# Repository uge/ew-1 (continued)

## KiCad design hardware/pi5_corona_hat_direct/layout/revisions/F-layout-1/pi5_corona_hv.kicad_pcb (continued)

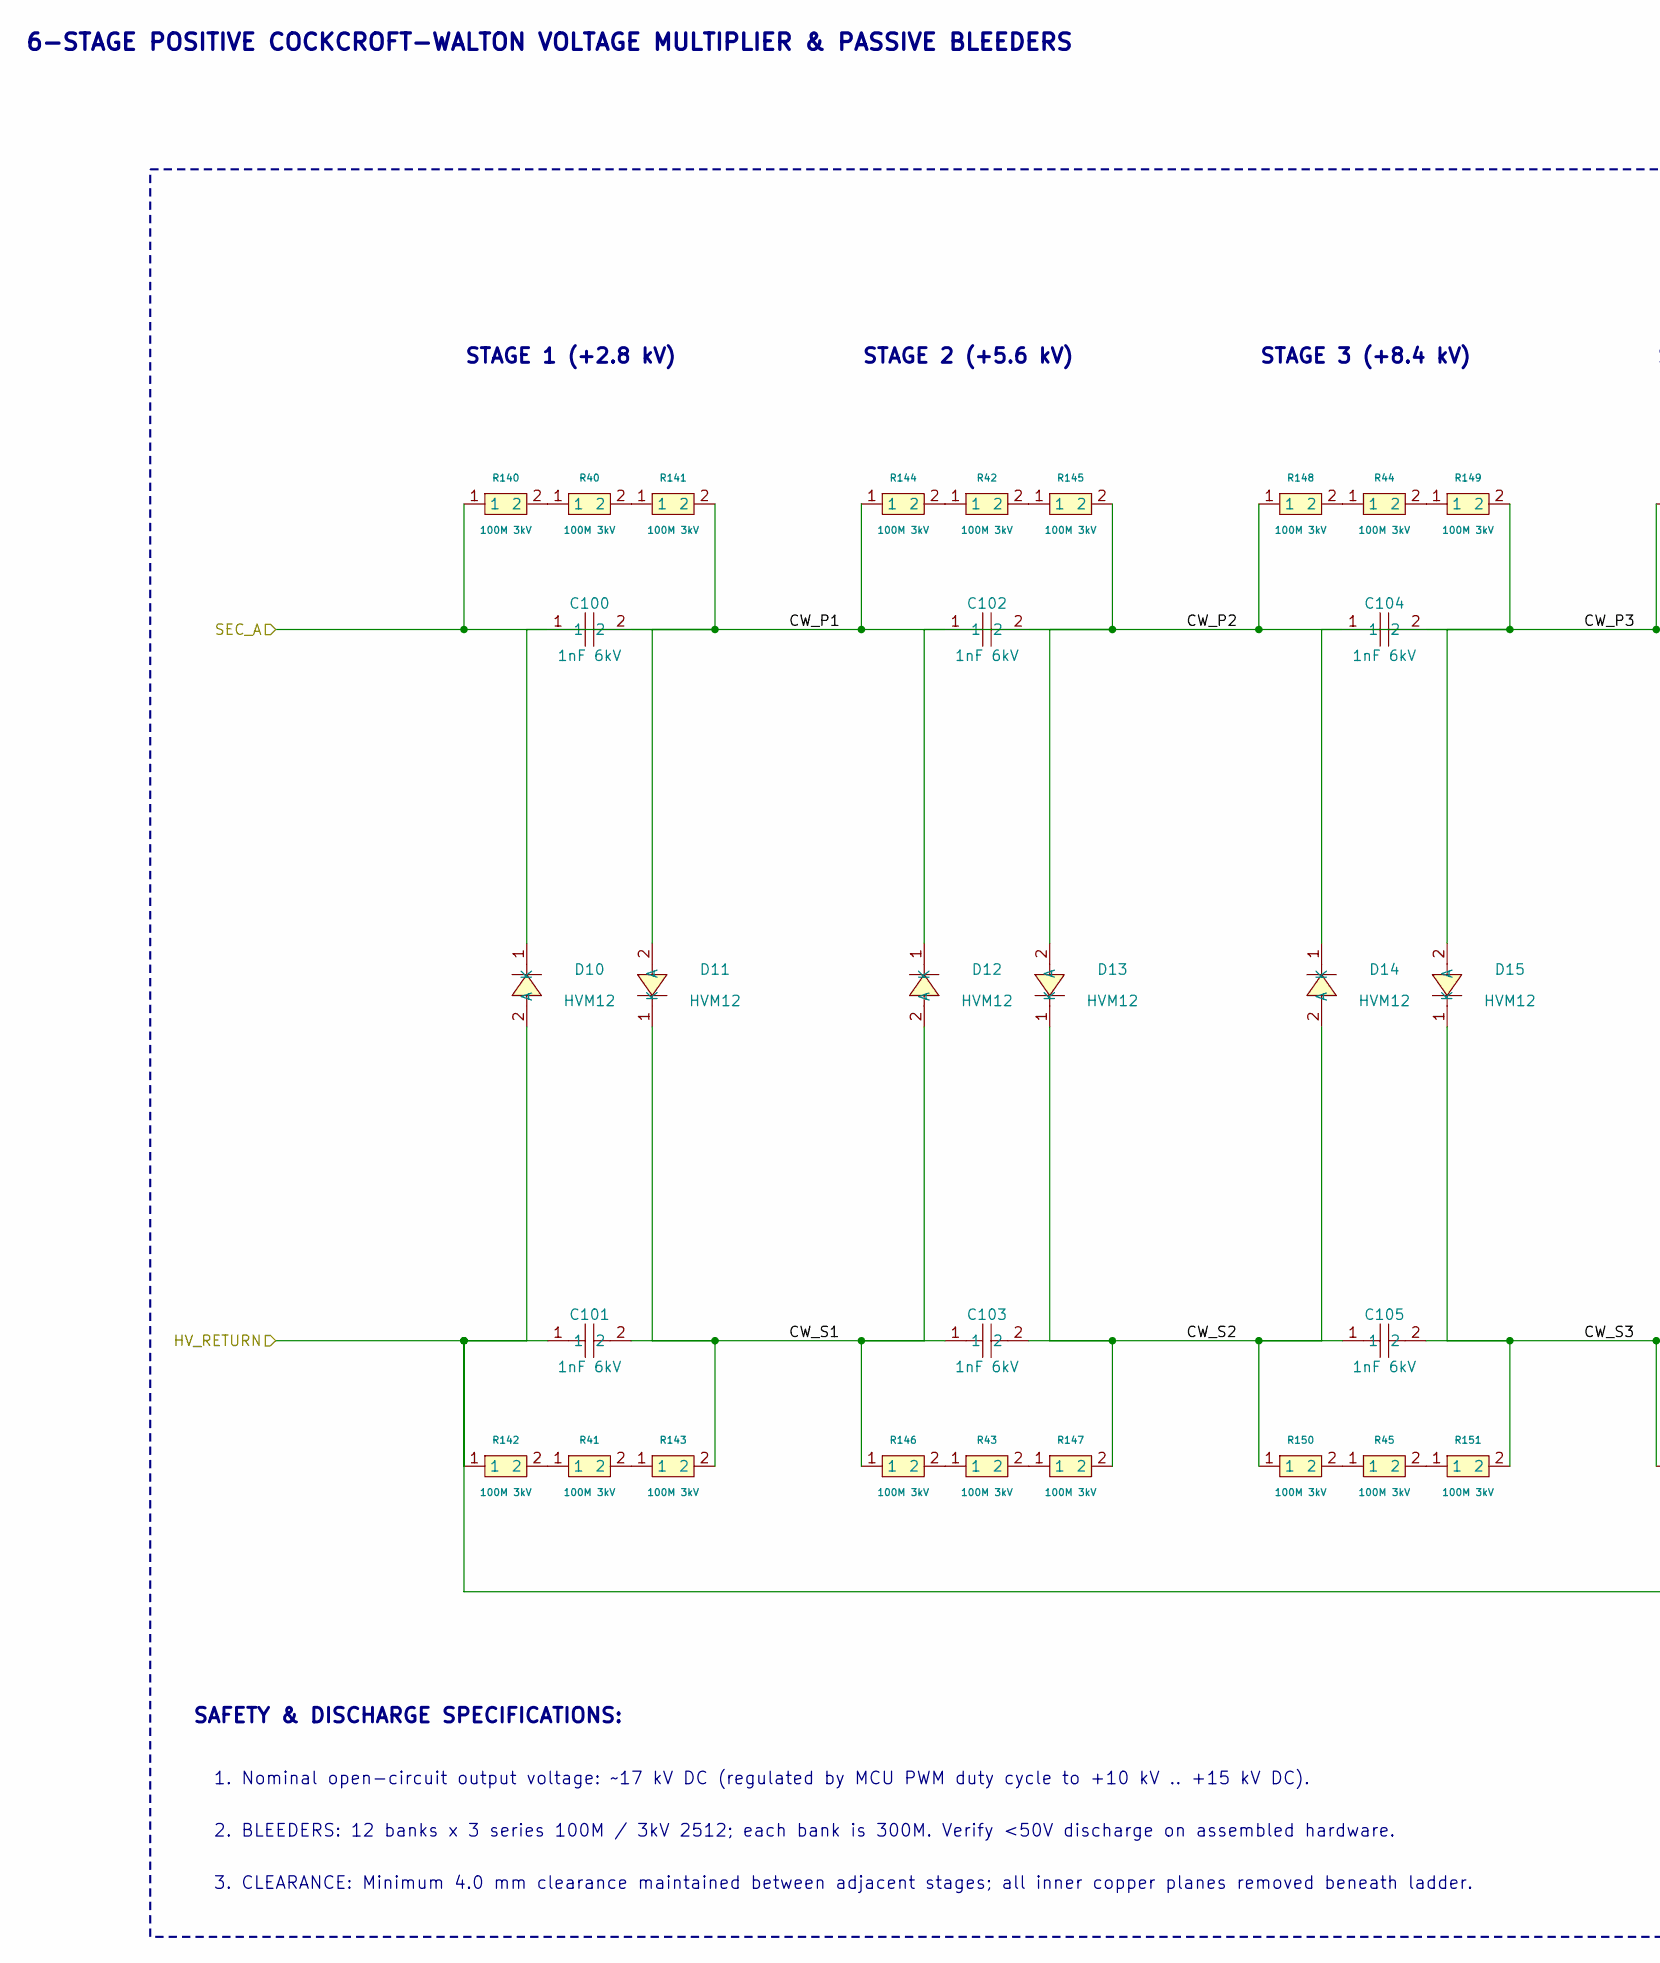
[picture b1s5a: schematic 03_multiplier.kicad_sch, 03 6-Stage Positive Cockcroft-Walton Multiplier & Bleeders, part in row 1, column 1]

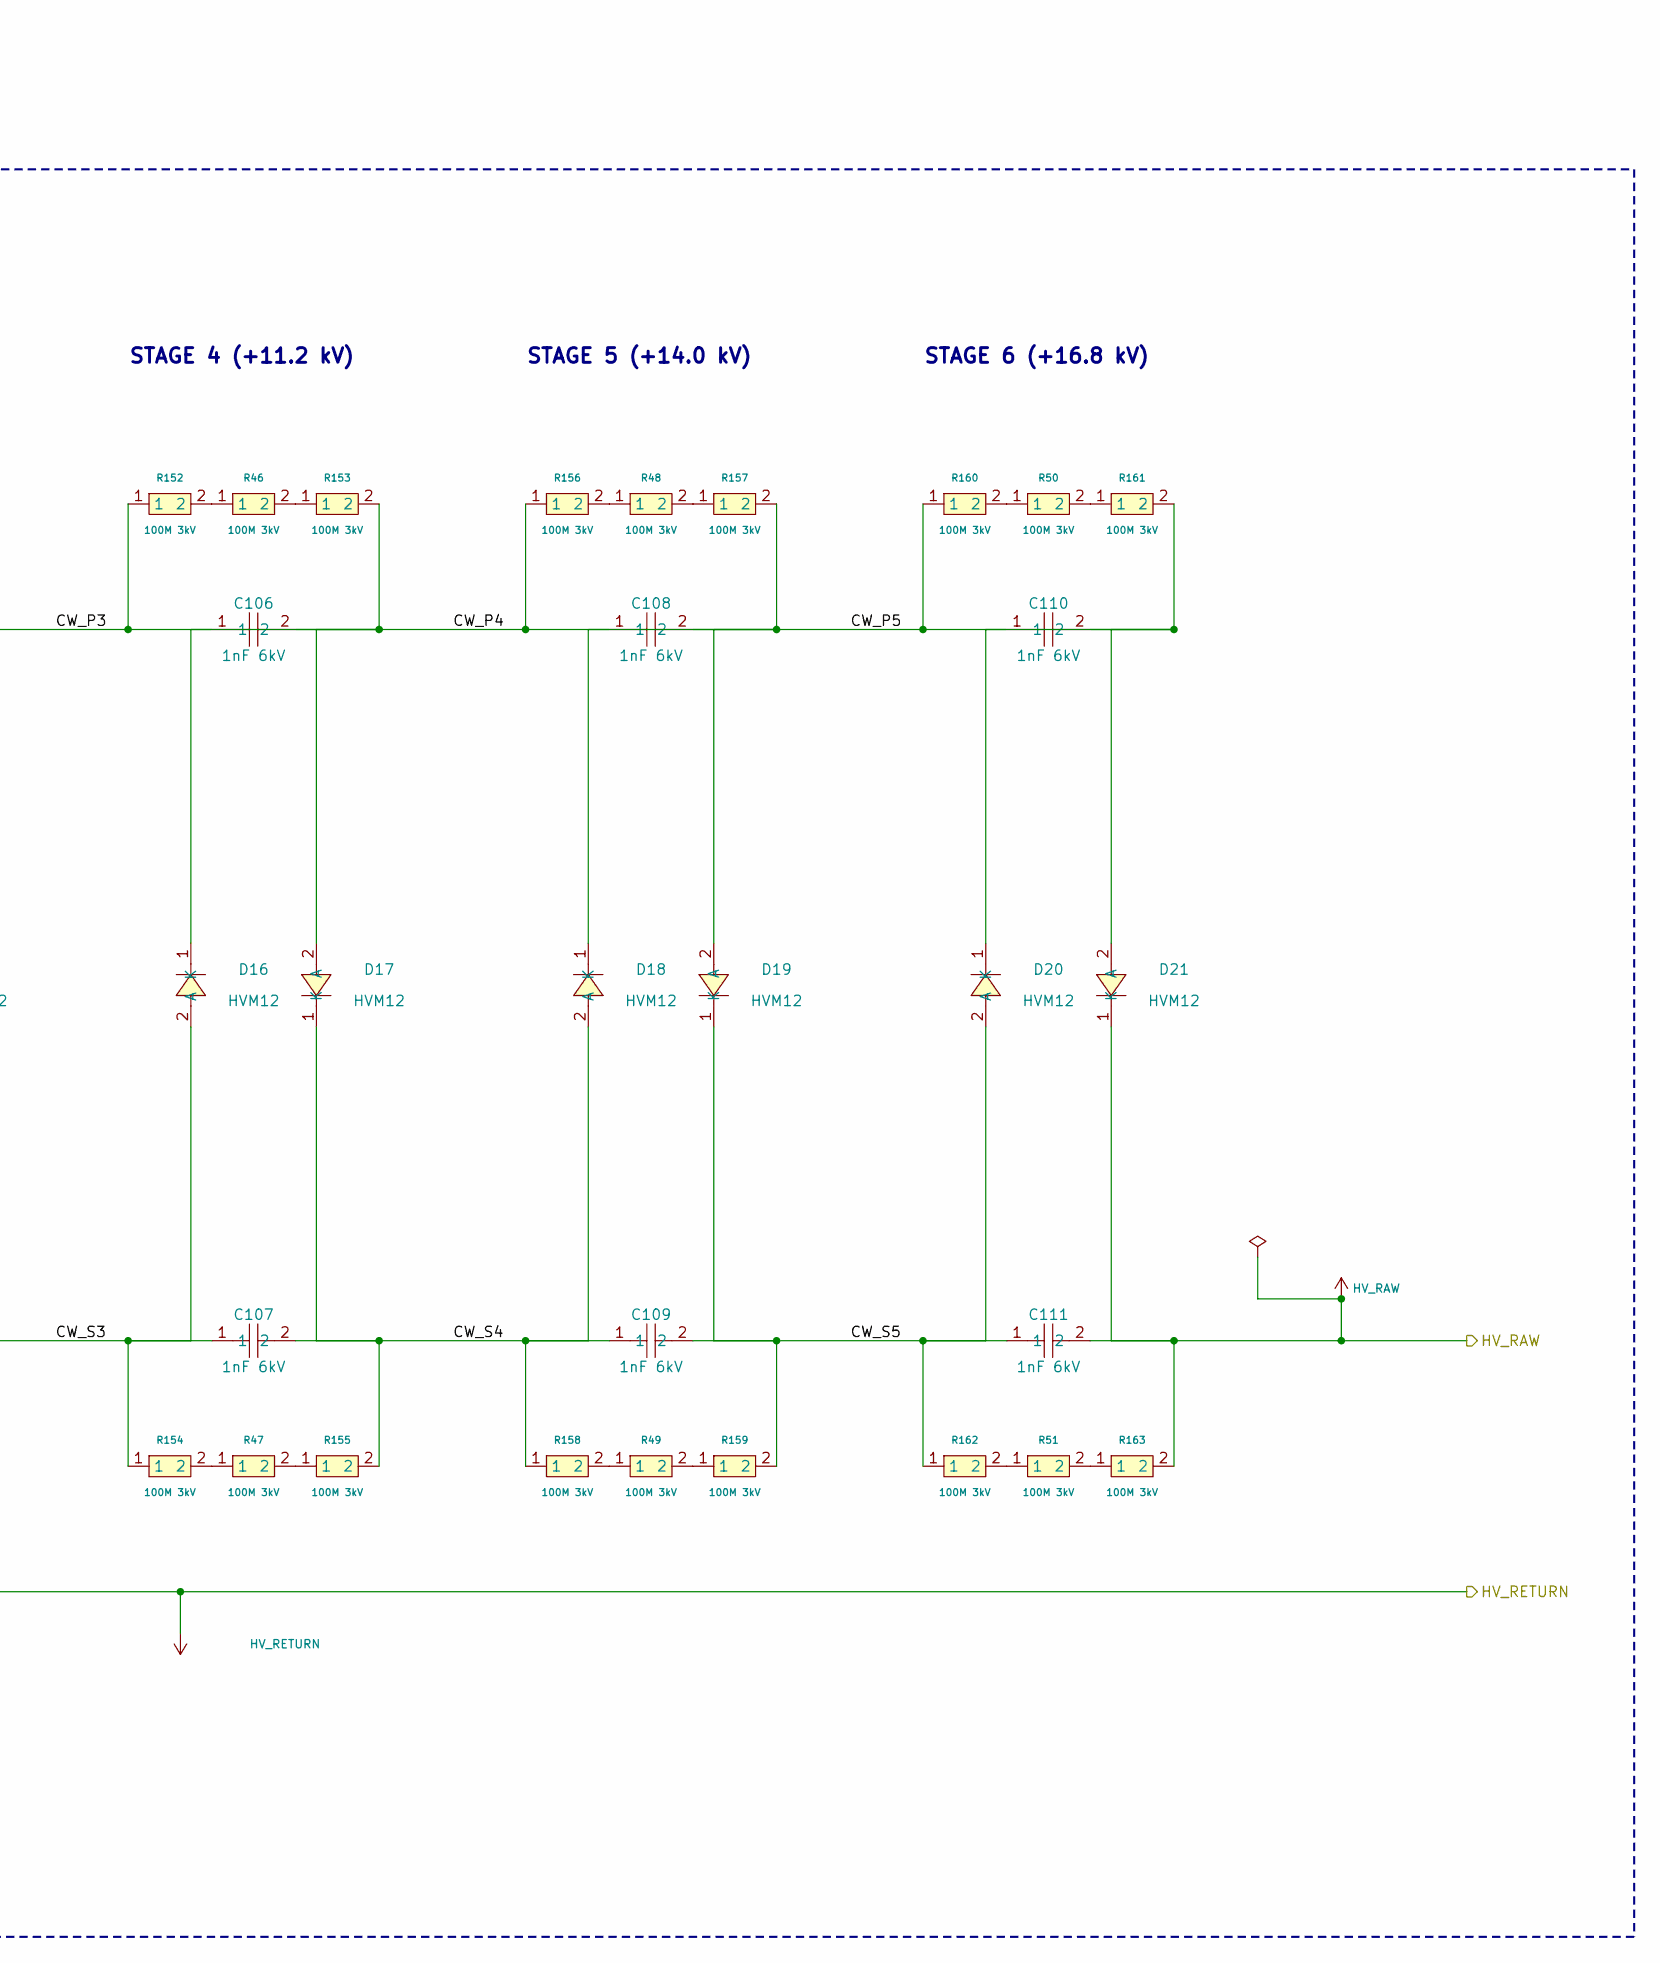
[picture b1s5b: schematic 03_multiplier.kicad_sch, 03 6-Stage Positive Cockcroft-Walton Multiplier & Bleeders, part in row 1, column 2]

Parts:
C100, C101, C102, C103, C104, C105, C106, C107, C108, C109, C110, C111: 1nF 6kV; CAP-TH_L15.0-W4.0-P10.00-D0.6; MPN S102M59Z5UU83L0R; LCSC Part C1620009
D10, D11, D12, D13, D14, D15, D16, D17, D18, D19, D20, D21: HVM12; DO-722_BD7.5-L22.0-P26.00-D1.2-RD; MPN HVM12; LCSC Part C7436450
R40, R41, R42, R43, R44, R45, R46, R47, R48, R49, R50, R51, R140, R141, R142, R143, R144, R145, R146, R147, R148, R149, R150, R151, R152, R153, R154, R155, R156, R157, R158, R159, R160, R161, R162, R163: 100M 3kV; R_2512_6332Metric; MPN CHV2512-JW-107ELF; LCSC Part C2089706

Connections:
/03_multiplier/CW_P1: C100.2, C102.1, D10.1 (K), D11.2 (A), R141.2, R144.1
/03_multiplier/CW_P2: C102.2, C104.1, D12.1 (K), D13.2 (A), R145.2, R148.1
/03_multiplier/CW_P3: C104.2, C106.1, D14.1 (K), D15.2 (A), R149.2, R152.1
/03_multiplier/CW_P4: C106.2, C108.1, D16.1 (K), D17.2 (A), R153.2, R156.1
/03_multiplier/CW_P5: C108.2, C110.1, D18.1 (K), D19.2 (A), R157.2, R160.1
/03_multiplier/CW_S1: C101.2, C103.1, D11.1 (K), D12.2 (A), R143.2, R146.1
/03_multiplier/CW_S2: C103.2, C105.1, D13.1 (K), D14.2 (A), R147.2, R150.1
/03_multiplier/CW_S3: C105.2, C107.1, D15.1 (K), D16.2 (A), R151.2, R154.1
/03_multiplier/CW_S4: C107.2, C109.1, D17.1 (K), D18.2 (A), R155.2, R158.1
/03_multiplier/CW_S5: C109.2, C111.1, D19.1 (K), D20.2 (A), R159.2, R162.1
/HV_RAW: C111.2, D21.1 (K), R163.2; also elsewhere on the board
/HV_RETURN: C101.1, D10.2 (A), R142.1; also elsewhere on the board
/SEC_A: C100.1, R140.1; also elsewhere on the board
unnamed: C110.2, D20.1 (K), D21.2 (A), R161.2
unnamed: R40.1, R140.2
unnamed: R40.2, R141.1
unnamed: R41.1, R142.2
unnamed: R41.2, R143.1
unnamed: R42.1, R144.2
unnamed: R42.2, R145.1
unnamed: R43.1, R146.2
unnamed: R43.2, R147.1
unnamed: R44.1, R148.2
unnamed: R44.2, R149.1
unnamed: R45.1, R150.2
unnamed: R45.2, R151.1
unnamed: R46.1, R152.2
unnamed: R46.2, R153.1
unnamed: R47.1, R154.2
unnamed: R47.2, R155.1
unnamed: R48.1, R156.2
unnamed: R48.2, R157.1
unnamed: R49.1, R158.2
unnamed: R49.2, R159.1
unnamed: R50.1, R160.2
unnamed: R50.2, R161.1
unnamed: R51.1, R162.2
unnamed: R51.2, R163.1

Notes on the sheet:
6-STAGE POSITIVE COCKCROFT-WALTON VOLTAGE MULTIPLIER & PASSIVE BLEEDERS
STAGE 1 (+2.8 kV)
STAGE 2 (+5.6 kV)
STAGE 3 (+8.4 kV)
STAGE 4 (+11.2 kV)
STAGE 5 (+14.0 kV)
STAGE 6 (+16.8 kV)
SAFETY & DISCHARGE SPECIFICATIONS:
1. Nominal open-circuit output voltage: ~17 kV DC (regulated by MCU PWM duty cycle to +10 kV .. +15 kV DC).
2. BLEEDERS: 12 banks x 3 series 100M / 3kV 2512; each bank is 300M. Verify <50V discharge on assembled hardware.
3. CLEARANCE: Minimum 4.0 mm clearance maintained between adjacent stages; all inner copper planes removed beneath ladder.

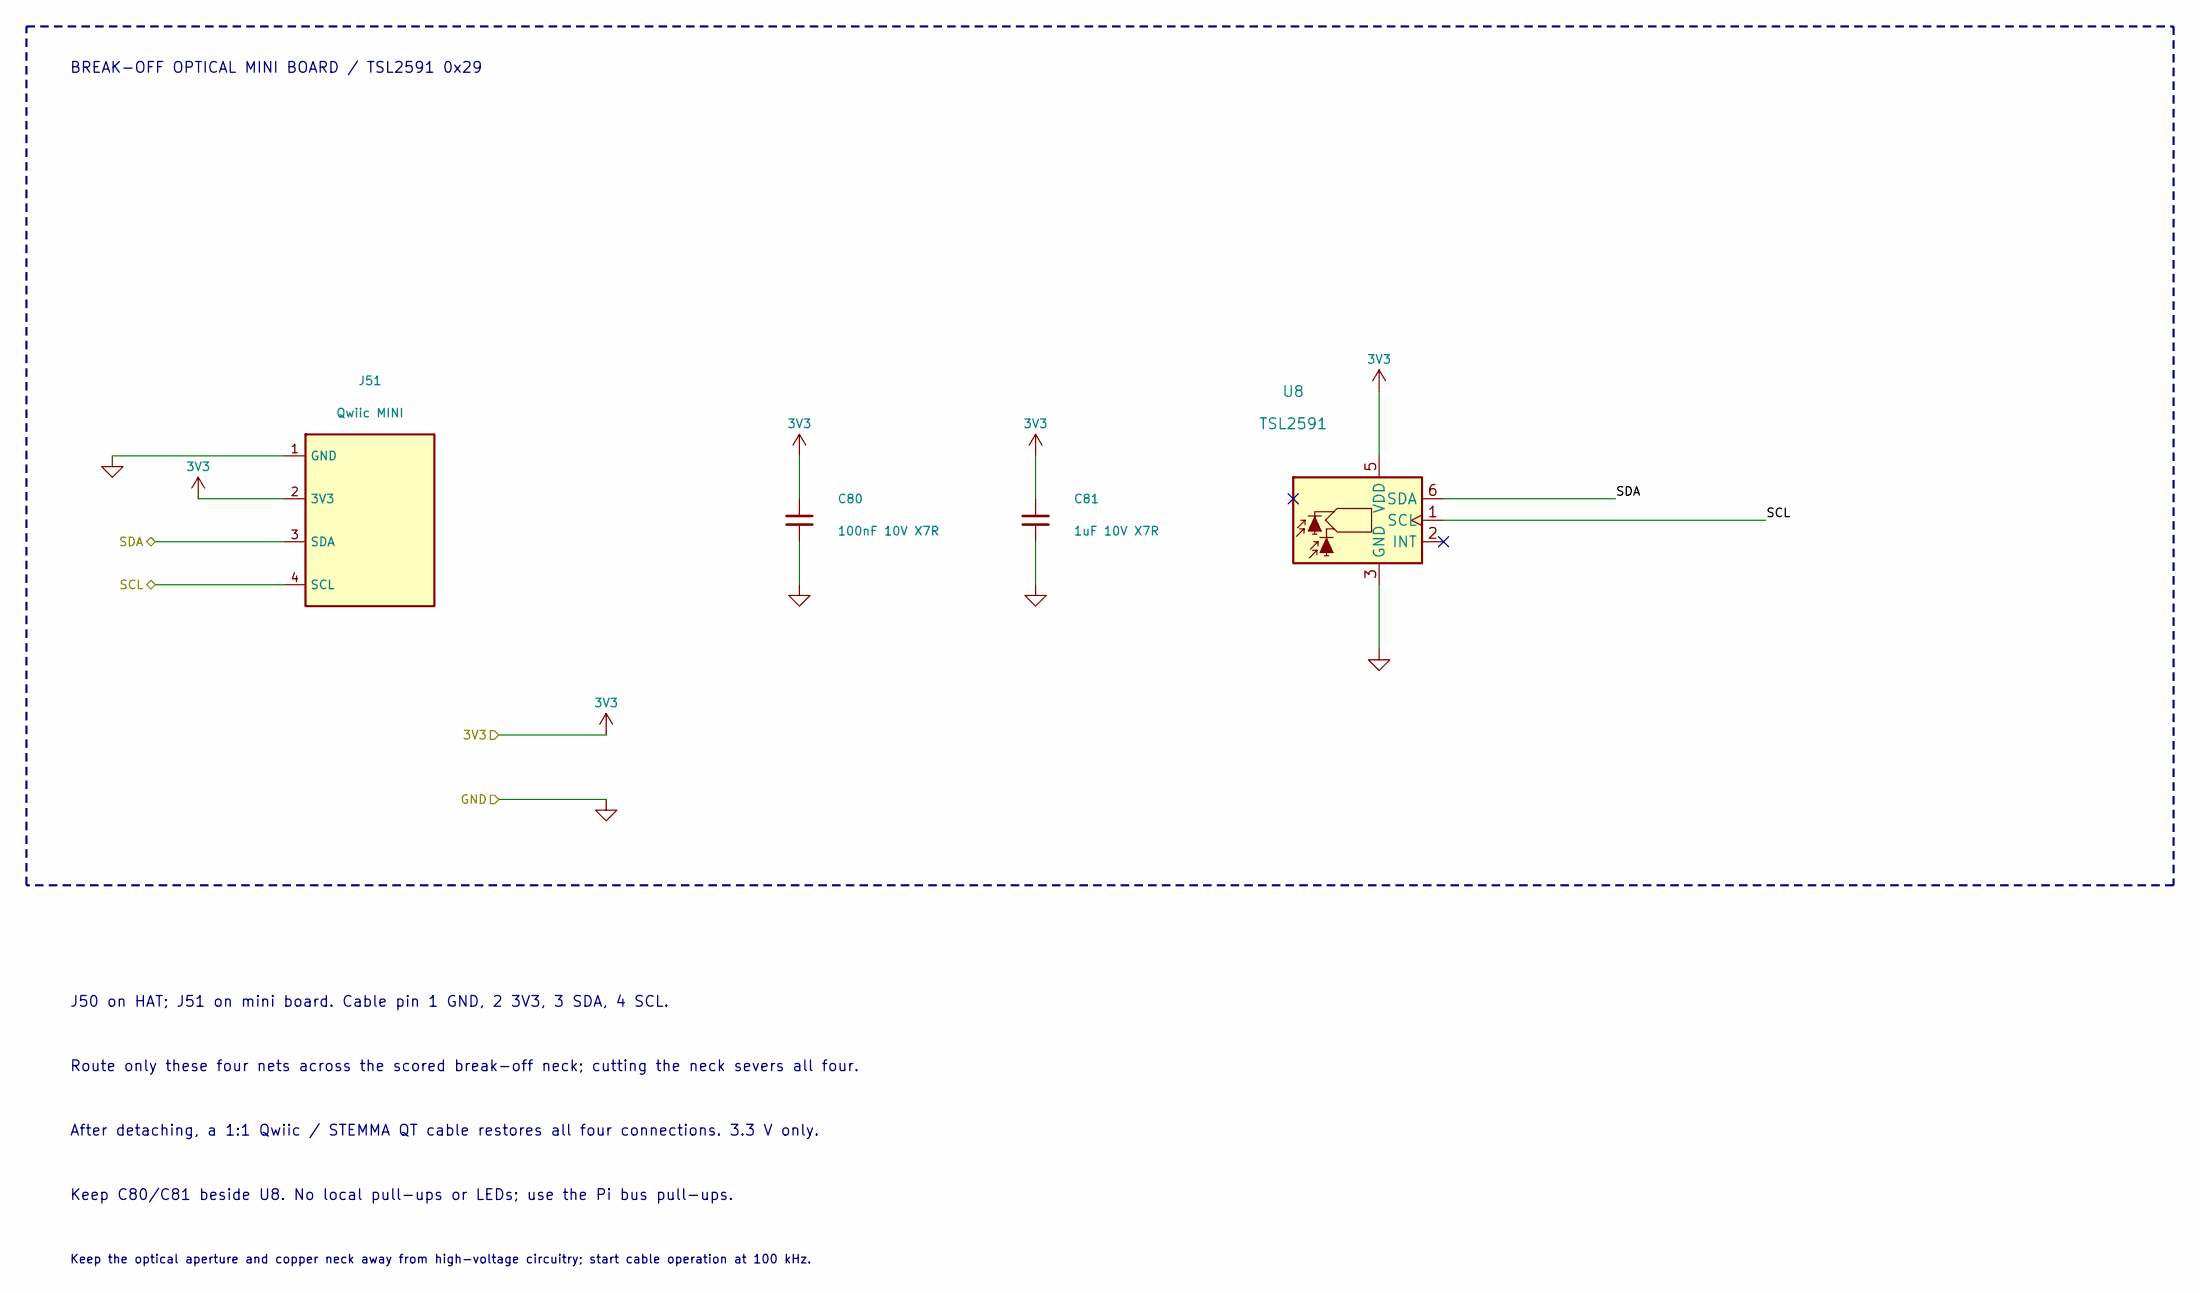
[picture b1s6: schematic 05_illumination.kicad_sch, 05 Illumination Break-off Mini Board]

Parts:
C80: 100nF 10V X7R; C_0603_1608Metric; MPN CC0603KRX7R9BB104; LCSC C14663
C81: 1uF 10V X7R; C_0603_1608Metric; MPN CL10B105KB8NQNC; LCSC C5199872
J51: Qwiic MINI; JST_SH_SM04B-SRSS-TB_1x04-1MP_P1.00mm_Horizontal; MPN SM04B-SRSS-TB(LF)(SN); LCSC C160404
U8: TSL2591; AMS_TSL25911FN; MPN TSL25911FN; LCSC C176812

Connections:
3V3: C80.1, C81.1, J51.2 (3V3), U8.5 (VDD); also elsewhere on the board
/01_power_mcu/SCL: J51.4 (SCL), U8.1 (SCL); also elsewhere on the board
/01_power_mcu/SDA: J51.3 (SDA), U8.6 (SDA); also elsewhere on the board
GND: C80.2, C81.2, J51.1 (GND), U8.3 (GND); also elsewhere on the board

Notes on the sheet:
BREAK-OFF OPTICAL MINI BOARD / TSL2591 0x29
J50 on HAT; J51 on mini board. Cable pin 1 GND, 2 3V3, 3 SDA, 4 SCL.
Route only these four nets across the scored break-off neck; cutting the neck severs all four.
After detaching, a 1:1 Qwiic / STEMMA QT cable restores all four connections. 3.3 V only.
Keep C80/C81 beside U8. No local pull-ups or LEDs; use the Pi bus pull-ups.
Keep the optical aperture and copper neck away from high-voltage circuitry; start cable operation at 100 kHz.

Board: 4 copper layers, 160 parts (1 on the bottom side), 103 nets, no tracks yet.

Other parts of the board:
H1, H2, H3, H4, H5, H6, H7: MountingHole_2.7mm_M2.5
MP1: Raspberry Pi 5 — DNP MECHANICAL; Raspberry_Pi_5_Mechanical
